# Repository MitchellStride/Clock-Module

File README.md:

# 🐦 Hummingbird RP2040 Clock Module ⏰

The **Hummingbird RP2040 Clock Module** is designed for crafting artisan clocks by pairing it with different clock faces. Its modular design allows this project to be shared across various display technologies.

The test OLED above shows time, my age, and my time to death countdown based on my life expectancy.

---

## 🔧 Features
- Raspberry Pi RP2040 microcontroller with dual-core ARM Cortex-M0+
- Highly compatible with JLCPCB's basic SMT components and 2L stackup for cost
- Powered via USB-C with ESD and reverse polarity protection
- DS1307Z+ RTC with CR2032 coin cell backup
- Single-sided design for a compact, flush mount
- Photocell/LDR support for automatic display dimming
- Additional features: piezoelectric buzzer, RGB LED, power switch, and optional OLED
- FFC expansion for modular clock face integration

---

## 📦 Status
> The PCBA has arrived, and is working, it needed one bodge. FW is done.

---

## 💡 Clock Ideas
Clocks I plan to build using this module:

<details>
<summary>Click to expand</summary>

- **Life Clock:** A countdown to estimated time of death using seven-segment displays
- **Nixie Clock:** A personal take on the classic Nixie tube clock, featuring IN-12 tubes
- **0402 Year Calendar** Inspired by the Yetch THE EVERY DAY GOAL CALENDAR

</details>

---

## 📝 Notes

<details>
<summary>Click to expand</summary>

- I had a few issues with the v1 hardware design since I completed it in roughly two days. Might do a v2.
- From 2024 (schematic design) to 2025 (layout), JLC PCB assembly changed many basic components and increased extended reel fees from $1 → $3, significantly affecting small-run costs.
- The cost per assembled PCB is approximately $8–10 USD, excluding setup fees. A total order of 2 PCBAs + 3 PCBs came to ~$57 + ~$17 shipping. After discounts, the total spent was ~$70 USD, plus $10–20 for extra parts from LCSC or Digikey. The largest expense was reel fees ($30).

See: -> ./images/cost2.png

</details>

---

## 🖼️ Image Appendix

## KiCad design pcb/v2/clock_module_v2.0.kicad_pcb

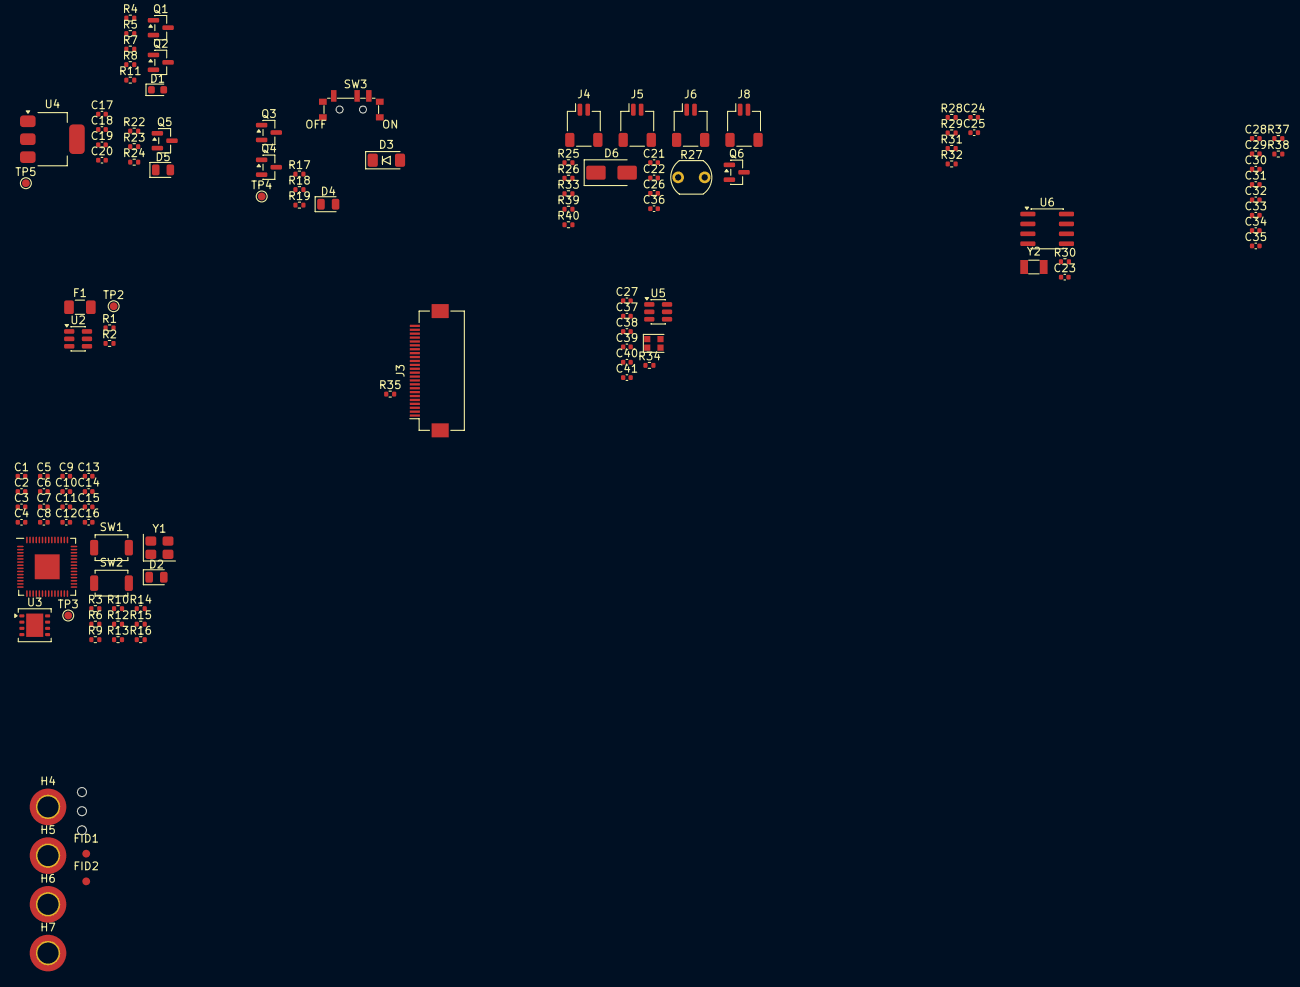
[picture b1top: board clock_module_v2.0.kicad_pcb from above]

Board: 4 copper layers, 121 parts (0 on the bottom side), 65 nets, no tracks yet.

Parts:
C1, C19, C26: 10u; C_0402_1005Metric
C2, C8, C16, C21, C23, C27, C28, C29, C31, C33, C34, C37, C38, C39, C40, C41: 1u; C_0402_1005Metric
C3, C4, C5, C6, C7, C9, C10, C11, C14, C15, C22, C24, C25, C30, C36: 0.1u; C_0402_1005Metric
C12, C13: 10p; C_0402_1005Metric
C17, C18, C20, C35: 4.7u; C_0402_1005Metric
C32: 2.2u; C_0402_1005Metric
D1: Red; LED_0603_1608Metric
D2: YLW; LED_0805_2012Metric
D3: 5.6V; D_MiniMELF
D4, D5: GRN; LED_0805_2012Metric
D6: SS14; D_SMA
D7: WS2812B-2020
F1: 12V 3A; Fuse_1206_3216Metric
FID1, FID2: Fiducial; Fiducial_1mm_Mask2mm
H1, H2, H3: Tooling_Hole_JLC; ToolingHole_1.152mm
H4, H5, H6, H7: Mounting_Hole; MountingHole_2.7mm_M2.5_DIN965_Pad_TopBottom
J3: FFC 24; Hirose_FH12-24S-0.5SH_1x24-1MP_P0.50mm_Horizontal
J4: PWR; JST_SH_SM02B-SRSS-TB_1x02-1MP_P1.00mm_Horizontal
J5: SW; JST_SH_SM02B-SRSS-TB_1x02-1MP_P1.00mm_Horizontal
J6, J8: LDR; JST_SH_SM02B-SRSS-TB_1x02-1MP_P1.00mm_Horizontal
Q1, Q2, Q5, Q6: AO3400A; SOT-23
Q3, Q4: AO3401A; SOT-23
R1, R2: 5.1k; R_0402_1005Metric
R3, R4, R13, R22, R26, R28, R31, R33, R40: 1k; R_0402_1005Metric
R5, R8, R17, R18, R23: 100k; R_0402_1005Metric
R6, R12, R25, R29, R30, R32, R37, R39: 10k; R_0402_1005Metric
R7, R11, R14, R19, R24: 2.2k; R_0402_1005Metric
R9, R10: 22; R_0402_1005Metric
R15, R16: 4.7k; R_0402_1005Metric
R27: GL5516; R_LDR_5.1x4.3mm_P3.4mm_Vertical
R34: 49.9; R_0402_1005Metric
R35: 0; R_0402_1005Metric
R38: 330k; R_0402_1005Metric
SW1, SW2: TS-1187A-B-A-B; SW_SPST_TS-1088-xR020
SW3: SSSS811101
TP2: VBUS; TestPoint_Pad_D1.0mm
TP3: RST; TestPoint_Pad_D1.0mm
TP4: 5V; TestPoint_Pad_D1.0mm
TP5: 3V3; TestPoint_Pad_D1.0mm
U1: RP2040; QFN-56_EP_7x7_Pitch0.4mm
U2: SRV05-4; SOT-23-6
U3: W25Q64JV; WSON-8-1EP_4x4mm_P0.8mm_EP2.2x3mm
U4: AMS1117-3.3; SOT-223-3_TabPin2
U5: SN74LVC1T45DBV; SOT-23-6
U6: DS1307Z+; SOIC-8_3.9x4.9mm_P1.27mm
Y1: XYDBPCNANF-12MHZ; Crystal_SMD_3225-4Pin_3.2x2.5mm
Y2: 32.768kHz; Crystal_SMD_3215-2Pin_3.2x1.5mm

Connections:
+3.3V: C16.1, R12.1, U1.1 (IOVDD), U1.10 (IOVDD), U1.22 (IOVDD), U1.33 (IOVDD), U1.42 (IOVDD), U1.43 (ADC_AVDD), U1.44 (VREG_VIN), U1.48 (USB_VDD), U1.49 (IOVDD), U3.8 (VDD)
+3V3: C1.1, C2.1, C3.1, C4.1, C6.1, C7.1, C9.1, C11.1, C15.1, C19.1, C20.1, C21.1, C28.1, C29.1, C31.1, C38.1, J3.4, R4.1, R6.1, R15.2, R16.2, R22.1, R26.2, R29.1, R30.1, R32.1, R37.1, R40.2, TP5.1, U4.2 (VO), U5.6 (VCCB)
+5V: C17.1, C18.1, C23.1, C26.1, C27.1, C37.1, C39.1, C40.1, C41.1, D6.1 (K), D7.4 (VDD), J3.3, J8.2, Q4.3 (D), R19.2, TP4.1, U4.3 (VI), U5.1 (VCCA), U6.8 (VCC)
/02 RP2040 & USB/D+: R10.2, U1.47 (USB_D+)
/02 RP2040 & USB/D-: R9.2, U1.46 (USB_D-)
/02 RP2040 & USB/GPIO25_LED: R14.2, U1.37 (GPIO25)
/02 RP2040 & USB/QSPI_SCLK: U1.52 (QSPI_SCLK), U3.6 (SCK)
/02 RP2040 & USB/QSPI_SD0: U1.53 (QSPI_SD0), U3.5 (DI/IO0)
/02 RP2040 & USB/QSPI_SD1: U1.55 (QSPI_SD1), U3.2 (DO/IO1)
/02 RP2040 & USB/QSPI_SD2: U1.54 (QSPI_SD2), U3.3 (~WP/IO2)
/02 RP2040 & USB/QSPI_SD3: U1.51 (QSPI_SD3), U3.7 (~HOLD/IO3)
/02 RP2040 & USB/USBBOOT: R13.2, SW2.2
/02 RP2040 & USB/USB_D+: R10.1, U2.3 (IO2)
/02 RP2040 & USB/USB_D-: R9.1, U2.1 (IO1)
/02 RP2040 & USB/~QSPI_CS: R12.2, R13.1, U1.56 (~QSPI_CS), U3.1 (~CS)
/02 RP2040 & USB/~RESET: C5.1, R3.2, R6.2, TP3.1, U1.26 (RUN)
/03 CONNS & PERIPHERALS/BUZZER_LOW: D6.2 (A), J8.1, Q6.3 (D)
/03 CONNS & PERIPHERALS/OLED_RST: C30.1, R37.2
GND: C1.2, C2.2, C3.2, C4.2, C5.2, C6.2, C7.2, C8.2, C9.2, C10.2, C11.2, C12.1, C13.1, C14.2, C15.2, C16.2, C17.2, C18.2, C19.2, C20.2, C21.2, C22.2, C23.2, C24.2, C25.2, C26.2, C27.2, C28.2, C29.2, C30.2, C31.2, C32.1, C35.1, C36.2, C37.2, C38.2, C39.2, C40.2, C41.2, D2.1 (K), D4.1 (K), D7.2 (VSS), J3.2, J3.5, J3.13, J3.18, J3.21, J3.24, J3.MP (MountingPoint), J4.1, J4.MP (Mounting_Point), J5.1, J5.MP (Mounting_Point), J6.MP (Mounting_Point), J8.MP (Mounting_Point), Q1.2 (S), Q2.2 (S), Q5.2 (S), Q6.2 (S), R1.2, R2.2, R5.2, R8.2, R23.2, R25.2, R38.1, R39.2, SW1.2, SW2.1, SW3.1 (A), SW3.2 (B), U1.19 (TESTEN), U1.57 (GND), U2.2 (VN), U3.4 (GND), U3.9 (GND), U4.1 (GND), U5.2 (GND), U5.5 (DIR), U6.4 (GND), Y1.2, Y1.4
GPIO2: J3.8, U1.4 (GPIO2)
GPIO3: J3.9, U1.5 (GPIO3)
GPIO4: J3.10, U1.6 (GPIO4)
GPIO5: J3.11, U1.7 (GPIO5)
GPIO6: J3.12, U1.8 (GPIO6)
GPIO7: J3.14, U1.9 (GPIO7)
GPIO8: J3.15, U1.11 (GPIO8)
GPIO9: J3.16, U1.12 (GPIO9)
GPIO10: J3.17, U1.13 (GPIO10)
GPIO11: R33.2, U1.14 (GPIO11)
GPIO12_PPS: R30.2, U1.15 (GPIO12), U6.7 (SQW/OUT)
GPIO13_WS2812_RGB_LED: U1.16 (GPIO13), U5.4 (B)
GPIO14_BUTTON_0: C24.1, R28.2, R29.2, U1.17 (GPIO14)
GPIO15_BUTTON_1: C25.1, R31.2, R32.2, U1.18 (GPIO15)
GPIO18: J3.19, U1.29 (GPIO18)
GPIO26_ADC0_LDR_EXT: C22.1, J6.1, R25.1, U1.38 (GPIO26)
GPIO27_ADC1_LDR: C36.1, R27.2, R39.1, U1.39 (GPIO27)
GPIO28_ADC2: J3.20, U1.40 (GPIO28)
I2C_SCL: J3.23, R15.1, U1.28 (GPIO17), U6.6 (SCL)
I2C_SDA: J3.22, R16.1, U1.27 (GPIO16), U6.5 (SDA)
unnamed: D1.2 (A), R11.1
unnamed: D1.1 (K), Q2.3 (D)
unnamed: D2.2 (A), R14.1
unnamed: D3.2 (A), Q3.1 (G), Q4.1 (G), R17.1
unnamed: D3.1 (K), Q3.2 (S), Q4.2 (S), R18.1
unnamed: D4.2 (A), R19.1
unnamed: D5.2 (A), R24.1
unnamed: D5.1 (K), Q5.3 (D)
unnamed: D7.3 (DIN), R34.1
unnamed: J3.7, R35.1
unnamed: J6.2, R26.1
unnamed: Q1.3 (D), Q2.1 (G), R7.1, R8.1
unnamed: Q1.1 (G), R4.2, R5.1
unnamed: Q5.1 (G), R22.2, R23.1
unnamed: Q6.1 (G), R33.1
unnamed: R3.1, SW1.1
unnamed: R27.1, R40.1
unnamed: C8.1, C10.1, C14.1, U1.23 (DVDD), U1.45 (VREG_VOUT), U1.50 (DVDD)
unnamed: C12.2, U1.20 (XIN), Y1.3
unnamed: C13.2, U1.21 (XOUT), Y1.1
unnamed: R34.2, U5.3 (A)
unnamed: U6.1 (X1), Y2.2
unnamed: U6.2 (X2), Y2.1
PWR_OFF_SW_N: J5.2, R17.2, R18.2, SW3.3 (C)
UNFUSED_VBUS: F1.2, J4.2
VBUS: F1.1, Q3.3 (D), R7.2, R11.2, R24.2, TP2.1, U2.5 (VP)

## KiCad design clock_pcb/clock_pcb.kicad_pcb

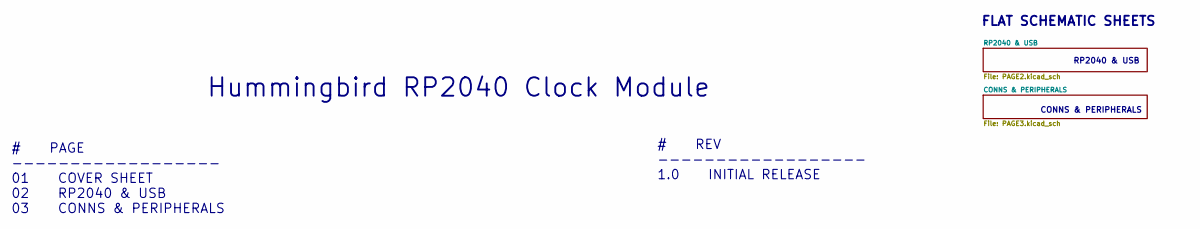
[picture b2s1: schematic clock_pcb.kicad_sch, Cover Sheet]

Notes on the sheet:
RP2040 & USB
CONNS & PERIPHERALS
Hummingbird RP2040 Clock Module
FLAT SCHEMATIC SHEETS
# REV ------------------ 1.0 INITIAL RELEASE
# PAGE ------------------ 01 COVER SHEET 02 RP2040 & USB 03 CONNS & PERIPHERALS

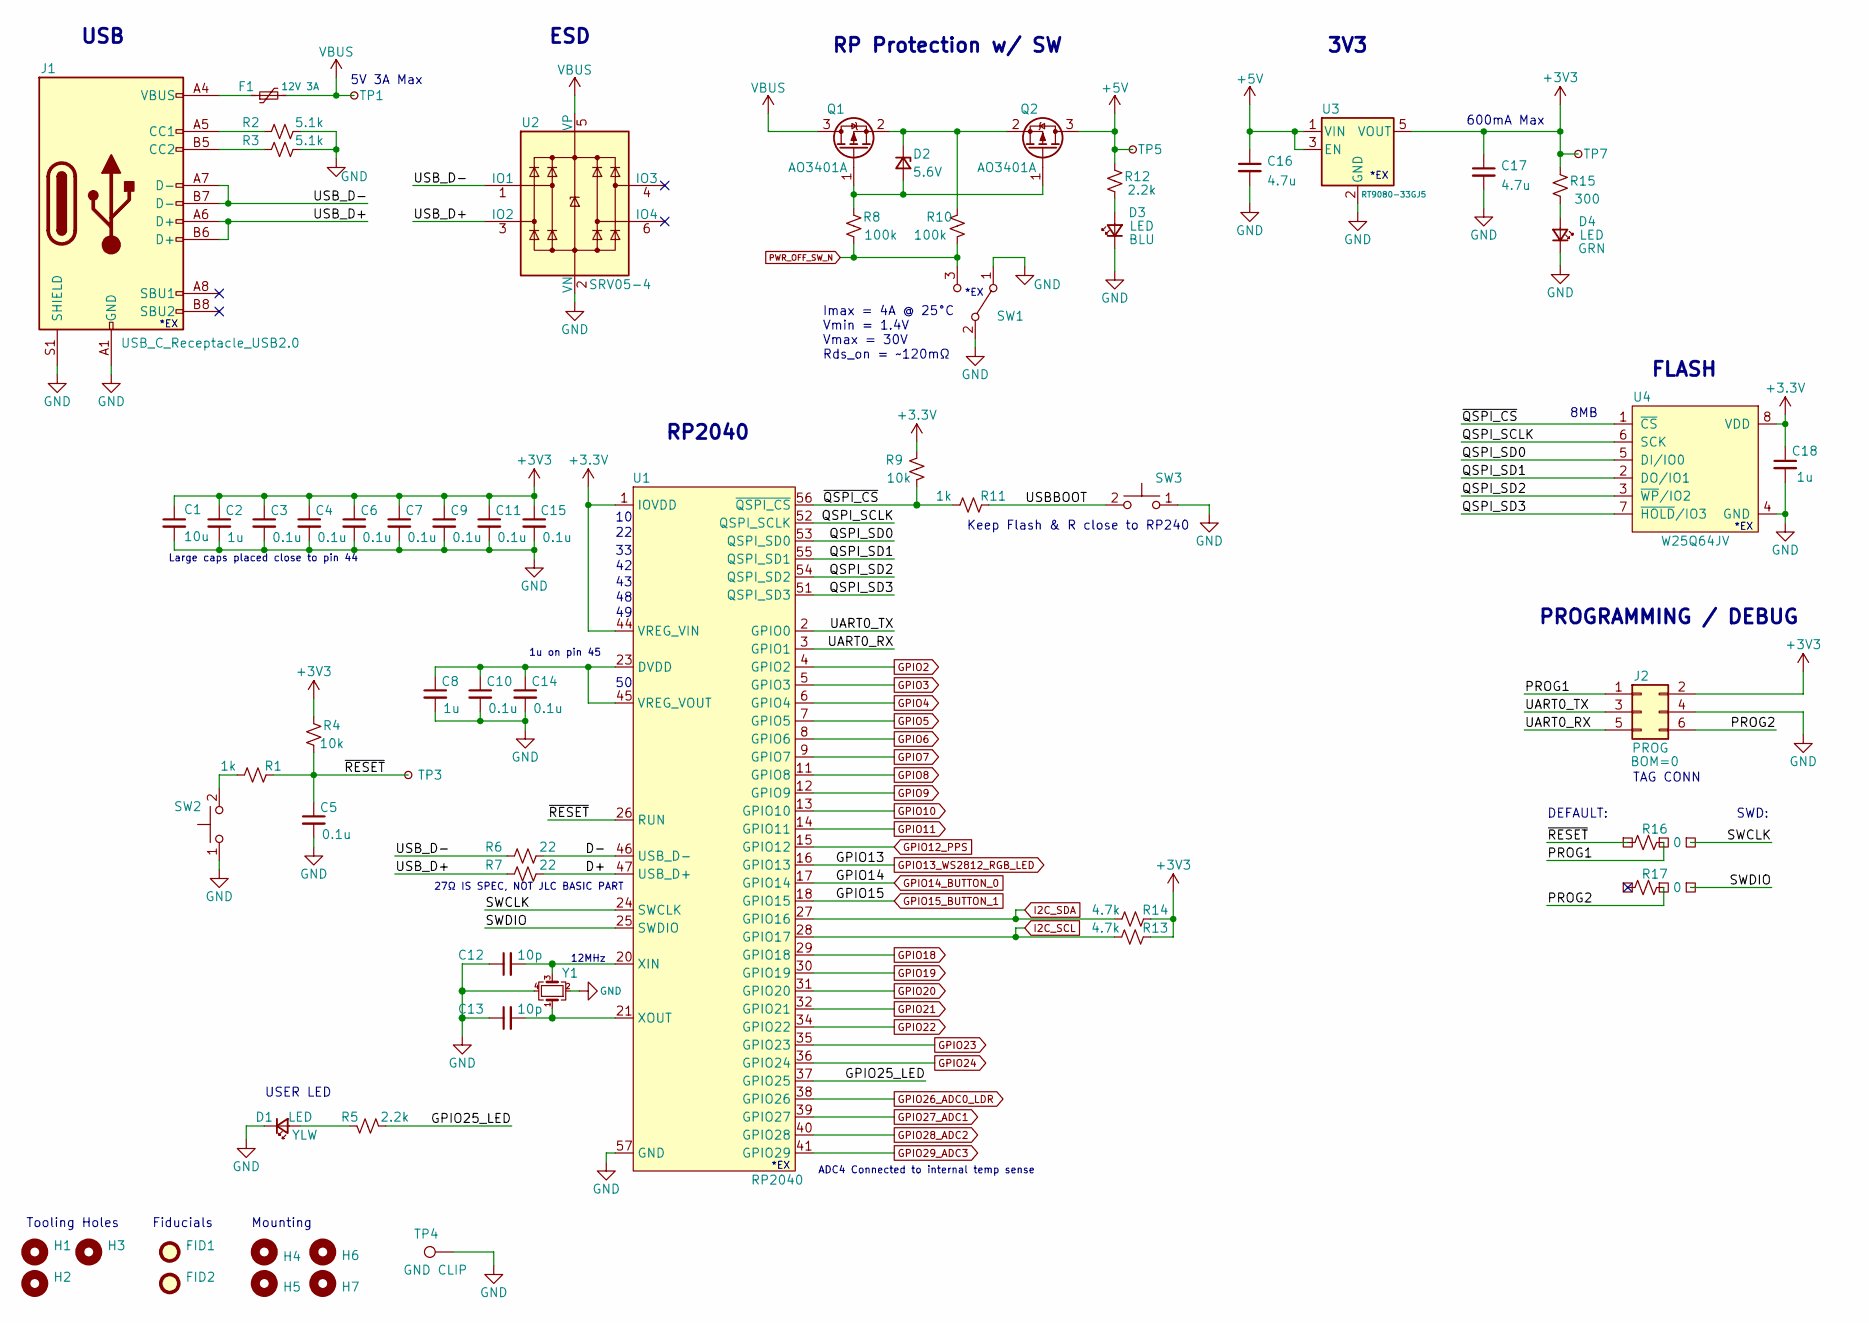
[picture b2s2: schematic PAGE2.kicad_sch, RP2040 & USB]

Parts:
C1: 10u; C_0402_1005Metric; lcsc C15525
C2, C8, C18: 1u; C_0402_1005Metric; lcsc C52923
C3, C4, C5, C6, C7, C9, C10, C11, C14, C15: 0.1u; C_0402_1005Metric; lcsc C1525
C12, C13: 10p; C_0402_1005Metric; lcsc C32949
C16, C17: 4.7u; C_0402_1005Metric; lcsc C23733
D1: LED; LED_0603_1608Metric; lcsc C72038
D2: 5.6V; D_MiniMELF; lcsc C8062
D3: LED; LED_0603_1608Metric; lcsc C72041
D4: LED; LED_0603_1608Metric; lcsc C72043
F1: 12V 3A; Fuse_1206_3216Metric; lcsc C516068
FID1, FID2: Fiducial; Fiducial_1mm_Mask2mm
H1, H2, H3: Tooling_Hole_JLC; JLC_Tooling_Hole
H4, H5, H6, H7: Mounting_Hole; MountingHole_2.7mm_M2.5
J1: USB_C_Receptacle_USB2.0; USB-C-16p_vertical_GT-USB-7051A; lcsc C2843970
J2: PROG; Tag-Connect_TC2030-IDC-NL_2x03_P1.27mm_Vertical
Q1, Q2: AO3401A; SOT-23; lcsc C15127
R1, R11: 1k; R_0402_1005Metric; lcsc C11702
R2, R3: 5.1k; R_0402_1005Metric; lcsc C25744
R4, R9: 10k; R_0402_1005Metric; lcsc C25744
R5, R12: 2.2k; R_0402_1005Metric; lcsc C25879
R6, R7: 22; R_0402_1005Metric; lcsc C25092
R8, R10: 100k; R_0402_1005Metric; lcsc C25741
R13, R14: 4.7k; R_0402_1005Metric; lcsc C25900
R15: 300; R_0402_1005Metric; lcsc C25102
R16, R17: 0; R_0402_1005Metric_3pad; lcsc C17168
SW1: SSSS811101; lcsc C109335
SW2, SW3: TS-1187A-B-A-B; SW_SPST_TL3342_RT; lcsc C318884
TP1: VBUS; TestPoint_Pad_D1.0mm
TP3: RST; TestPoint_Pad_D1.0mm
TP4: GND CLIP; ronghe_RH-5016_C5199799; lcsc C5199799
TP5: 5V; TestPoint_Pad_D1.0mm
TP7: 3V3; TestPoint_Pad_D1.0mm
U1: RP2040; QFN-56_EP_7x7_Pitch0.4mm; lcsc C2040
U2: SRV05-4; SOT-23-6; lcsc C85364
U3: RT9080-33GJ5; SOT-23-5; lcsc C841192
U4: W25Q64JV; WSON-8-1EP_4x4mm_P0.8mm_EP2.2x3mm; lcsc C2940195
Y1: XYDBPCNANF-12MHZ; Crystal_SMD_3225-4Pin_3.2x2.5mm; lcsc C9002

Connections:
+5V: C16.1, Q2.3 (D), R12.2, TP5.1, U3.1 (VIN), U3.3 (EN); also elsewhere on the board
/RP2040 & USB/D+: R7.2, U1.47 (USB_D+)
/RP2040 & USB/D-: R6.2, U1.46 (USB_D-)
/RP2040 & USB/GPIO25_LED: R5.2, U1.37 (GPIO25)
/RP2040 & USB/PROG1: J2.1, R16.2
/RP2040 & USB/PROG2: J2.6, R17.2
/RP2040 & USB/QSPI_SCLK: U1.52 (QSPI_SCLK), U4.6 (SCK)
/RP2040 & USB/QSPI_SD0: U1.53 (QSPI_SD0), U4.5 (DI/IO0)
/RP2040 & USB/QSPI_SD1: U1.55 (QSPI_SD1), U4.2 (DO/IO1)
/RP2040 & USB/QSPI_SD2: U1.54 (QSPI_SD2), U4.3 (~WP/IO2)
/RP2040 & USB/QSPI_SD3: U1.51 (QSPI_SD3), U4.7 (~HOLD/IO3)
/RP2040 & USB/SWCLK: R16.3, U1.24 (SWCLK)
/RP2040 & USB/SWDIO: R17.3, U1.25 (SWDIO)
/RP2040 & USB/UART0_RX: J2.5, U1.3 (GPIO1)
/RP2040 & USB/UART0_TX: J2.3, U1.2 (GPIO0)
/RP2040 & USB/USBBOOT: R11.2, SW3.2
/RP2040 & USB/USB_D+: J1.A6 (D+), J1.B6 (D+), R7.1, U2.3 (IO2)
/RP2040 & USB/USB_D-: J1.A7 (D-), J1.B7 (D-), R6.1, U2.1 (IO1)
/RP2040 & USB/~QSPI_CS: R9.2, R11.1, U1.56 (~QSPI_CS), U4.1 (~CS)
/RP2040 & USB/~RESET: C5.1, R1.2, R4.2, R16.1, TP3.1, U1.26 (RUN)
GND: C1.2, C2.2, C3.2, C4.2, C5.2, C6.2, C7.2, C8.2, C9.2, C10.2, C11.2, C12.1, C13.1, C14.2, C15.2, C16.2, C17.2, C18.2, D1.1 (K), D3.1 (K), D4.1 (K), J1.A1 (GND), J1.A12 (GND), J1.B1 (GND), J1.B12 (GND), J1.S1 (SHIELD), J2.4, R2.2, R3.2, SW1.1 (A), SW1.2 (B), SW2.1, SW3.1, TP4.1, U1.19 (TESTEN), U1.57 (GND), U2.2 (VN), U3.2 (GND), U4.4 (GND), U4.9 (GND), Y1.2, Y1.4; also elsewhere on the board
GPIO2: U1.4 (GPIO2); also elsewhere on the board
GPIO3: U1.5 (GPIO3); also elsewhere on the board
GPIO4: U1.6 (GPIO4); also elsewhere on the board
GPIO5: U1.7 (GPIO5); also elsewhere on the board
GPIO6: U1.8 (GPIO6); also elsewhere on the board
GPIO7: U1.9 (GPIO7); also elsewhere on the board
GPIO8: U1.11 (GPIO8); also elsewhere on the board
GPIO9: U1.12 (GPIO9); also elsewhere on the board
GPIO10: U1.13 (GPIO10); also elsewhere on the board
GPIO11: U1.14 (GPIO11); also elsewhere on the board
GPIO12_PPS: U1.15 (GPIO12)
GPIO13_WS2812_RGB_LED: U1.16 (GPIO13); also elsewhere on the board
GPIO14_BUTTON_0: U1.17 (GPIO14)
GPIO15_BUTTON_1: U1.18 (GPIO15)
GPIO18: U1.29 (GPIO18)
GPIO19: U1.30 (GPIO19)
GPIO20: U1.31 (GPIO20)
GPIO21: U1.32 (GPIO21)
GPIO22: U1.34 (GPIO22)
GPIO23: U1.35 (GPIO23)
GPIO24: U1.36 (GPIO24)
GPIO26_ADC0_LDR: U1.38 (GPIO26); also elsewhere on the board
GPIO27_ADC1: U1.39 (GPIO27); also elsewhere on the board
GPIO28_ADC2: U1.40 (GPIO28); also elsewhere on the board
GPIO29_ADC3: U1.41 (GPIO29)
I2C_SCL: R13.1, U1.28 (GPIO17); also elsewhere on the board
I2C_SDA: R14.1, U1.27 (GPIO16); also elsewhere on the board
unnamed: D1.2 (A), R5.1
unnamed: D2.2 (A), Q1.1 (G), Q2.1 (G), R8.1
unnamed: D2.1 (K), Q1.2 (S), Q2.2 (S), R10.1
unnamed: D3.2 (A), R12.1
unnamed: D4.2 (A), R15.1
unnamed: F1.1, J1.A4 (VBUS), J1.A9 (VBUS), J1.B4 (VBUS), J1.B9 (VBUS)
unnamed: J1.A5 (CC1), R2.1
unnamed: J1.B5 (CC2), R3.1
unnamed: R1.1, SW2.2
unnamed: C8.1, C10.1, C14.1, U1.23 (DVDD), U1.45 (VREG_VOUT), U1.50 (DVDD)
unnamed: C12.2, U1.20 (XIN), Y1.3
unnamed: C13.2, U1.21 (XOUT), Y1.1
PWR_OFF_SW_N: R8.2, R10.2, SW1.3 (C); also elsewhere on the board
VBUS: F1.2, Q1.3 (D), TP1.1, U2.5 (VP); also elsewhere on the board

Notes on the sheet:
12MHz
5V 3A Max
3V3
8MB
*EX
Imax = 4A @ 25°C Vmin = 1.4V Vmax = 30V Rds_on = ~120mΩ
RP Protection w/ SW
27Ω IS SPEC, NOT JLC BASIC PART
Tooling Holes
ADC4 Connected to internal temp sense
ESD
Keep Flash & R close to RP240
USB
TAG CONN
Mounting
Large caps placed close to pin 44
FLASH
DEFAULT:
1u on pin 45
RP2040
600mA Max
USER LED
Fiducials
PROGRAMMING / DEBUG
SWD:

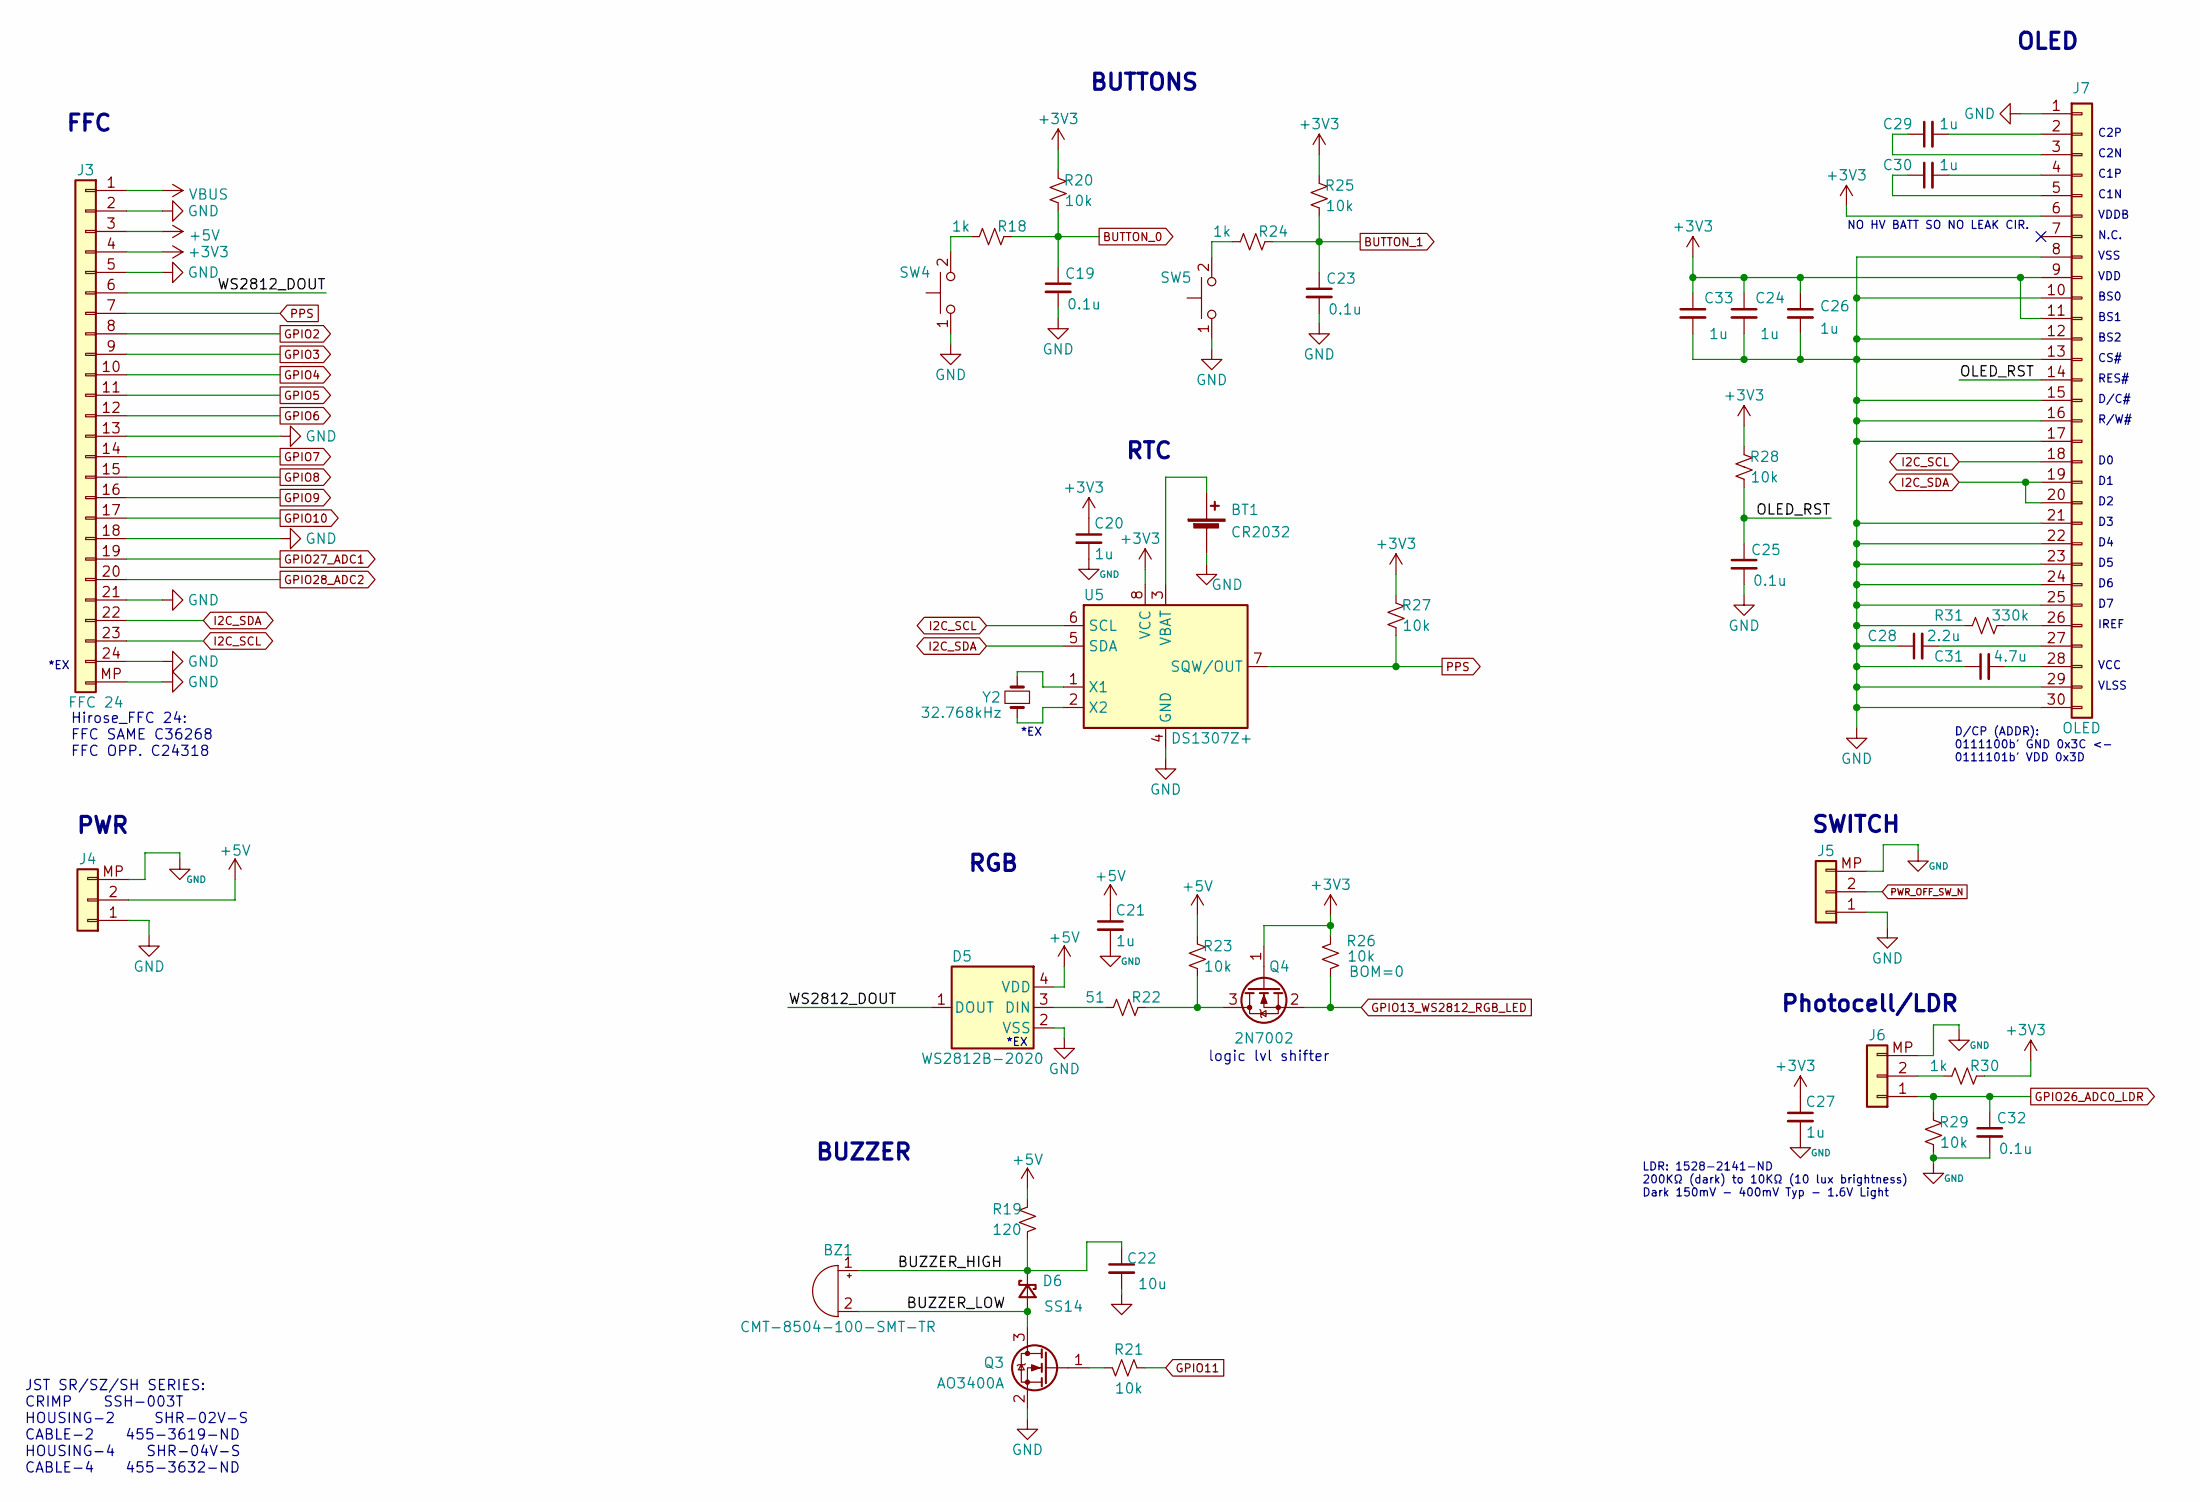
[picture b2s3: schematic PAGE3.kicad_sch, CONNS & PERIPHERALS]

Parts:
BT1: CR2032; Q&J_CR2032-BS-6-1; lcsc C70377
BZ1: CMT-8504-100-SMT-TR; MagneticBuzzer_CUI_CMT-8504-100-SMT; digi 102-CMT-8504-100-SMT-CT-ND
C19, C23, C25, C32: 0.1u; C_0402_1005Metric; lcsc C1525
C20, C21, C24, C26, C27, C29, C30, C33: 1u; C_0402_1005Metric; lcsc C52923
C22: 10u; C_0402_1005Metric; lcsc C15525
C28: 2.2u; C_0402_1005Metric; lcsc C12530
C31: 4.7u; C_0402_1005Metric; lcsc C23733
D5: WS2812B-2020; lcsc C965555
D6: SS14; D_SMA; lcsc C2480
J3: FFC 24; Hirose_FH12-24S-0.5SH_1x24-1MP_P0.50mm_Horizontal; lcsc C202112
J4, J5, J6: 5V; JST_SH_SM02B-SRSS-TB_1x02-1MP_P1.00mm_Horizontal; lcsc C160402
J7: OLED; OLED-128O064D_edit_reverse_v2; lcsc C2890596
Q3: AO3400A; SOT-23; lcsc C20917
Q4: 2N7002; SOT-23; lcsc C8545
R18, R24, R30: 1k; R_0402_1005Metric; lcsc C11702
R19: 120; R_0402_1005Metric; lcsc C25079
R20, R21, R23, R25, R26, R27, R28, R29: 10k; R_0402_1005Metric; lcsc C25744
R22: 51; R_0402_1005Metric; lcsc C25125
R31: 330k; R_0402_1005Metric; lcsc C25778
SW4, SW5: TS-1187A-B-A-B; SW_SPST_TL3342_RT; lcsc C318884
U5: DS1307Z+; SOIC-8_3.9x4.9mm_P1.27mm; lcsc C8959
Y2: 32.768kHz; Crystal_SMD_3215-2Pin_3.2x1.5mm; lcsc C95361

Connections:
+5V: C21.1, D5.4 (VDD), J3.3, J4.2, R19.1, R23.1; also elsewhere on the board
/CONNS & PERIPHERALS/BUZZER_HIGH: BZ1.1 (-), C22.1, D6.1 (K), R19.2
/CONNS & PERIPHERALS/BUZZER_LOW: BZ1.2 (+), BZ1.3 (DUMMY1), BZ1.4 (DUMMY2), D6.2 (A), Q3.3 (D)
/CONNS & PERIPHERALS/OLED_RST: C25.1, J7.14, R28.2
/CONNS & PERIPHERALS/WS2812_DOUT: D5.1 (DOUT), J3.6
BUTTON_0: C19.1, R18.2, R20.2
BUTTON_1: C23.1, R24.2, R25.2
GND: BT1.2 (-), C19.2, C20.2, C21.2, C22.2, C23.2, C24.2, C25.2, C26.2, C27.2, C28.1, C31.1, C32.2, C33.2, D5.2 (VSS), J3.2, J3.5, J3.13, J3.18, J3.21, J3.24, J3.MP (MountingPoint), J4.1, J4.MP (Mounting_Point), J5.1, J5.MP (Mounting_Point), J6.MP (Mounting_Point), J7.1, J7.8, J7.10, J7.12, J7.13, J7.15, J7.16, J7.17, J7.21, J7.22, J7.23, J7.24, J7.25, J7.29, J7.30, Q3.2 (S), R29.2, R31.1, SW4.1, SW5.1, U5.4 (GND); also elsewhere on the board
GPIO2: J3.8; also elsewhere on the board
GPIO3: J3.9; also elsewhere on the board
GPIO4: J3.10; also elsewhere on the board
GPIO5: J3.11; also elsewhere on the board
GPIO6: J3.12; also elsewhere on the board
GPIO7: J3.14; also elsewhere on the board
GPIO8: J3.15; also elsewhere on the board
GPIO9: J3.16; also elsewhere on the board
GPIO10: J3.17; also elsewhere on the board
GPIO11: R21.1; also elsewhere on the board
GPIO13_WS2812_RGB_LED: Q4.2 (S), R26.2; also elsewhere on the board
GPIO26_ADC0_LDR: C32.1, J6.1, R29.1; also elsewhere on the board
GPIO27_ADC1: J3.19; also elsewhere on the board
GPIO28_ADC2: J3.20; also elsewhere on the board
I2C_SCL: J3.23, J7.18, U5.6 (SCL); also elsewhere on the board
I2C_SDA: J3.22, J7.19, J7.20, U5.5 (SDA); also elsewhere on the board
unnamed: BT1.1 (+), U5.3 (VBAT)
unnamed: D5.3 (DIN), R22.1
unnamed: J6.2, R30.1
unnamed: C29.2, J7.2
unnamed: C29.1, J7.3
unnamed: C30.2, J7.4
unnamed: C30.1, J7.5
unnamed: J7.26, R31.2
unnamed: C28.2, J7.27
unnamed: C31.2, J7.28
unnamed: Q3.1 (G), R21.2
unnamed: Q4.3 (D), R22.2, R23.2
unnamed: R18.1, SW4.2
unnamed: R24.1, SW5.2
unnamed: U5.1 (X1), Y2.2
unnamed: U5.2 (X2), Y2.1
PPS: J3.7, R27.2, U5.7 (SQW/OUT)
PWR_OFF_SW_N: J5.2; also elsewhere on the board
VBUS: J3.1; also elsewhere on the board

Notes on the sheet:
VCC
BS2
PWR
OLED
*EX
SWITCH
BUZZER
RES#
R/W#
C1N
CS#
Photocell/LDR
NO HV BATT SO NO LEAK CIR.
logic lvl shifter
BS1
FFC
IREF
D/CP (ADDR): 0111100b' GND 0x3C <- 0111101b' VDD 0x3D
D/C#
VDDB
BS0
C2N
RTC
C1P
BUTTONS
LDR: 1528-2141-ND 200KΩ (dark) to 10KΩ (10 lux brightness) Dark 150mV - 400mV Typ - 1.6V Light
Hirose_FFC 24: FFC SAME C36268 FFC OPP. C24318
VLSS
VSS
C2P
JST SR/SZ/SH SERIES: CRIMP SSH-003T HOUSING-2 SHR-02V-S CABLE-2 455-3619-ND HOUSING-4 SHR-04V-S CABLE-4 455-3632-ND
N.C.
RGB
VDD

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
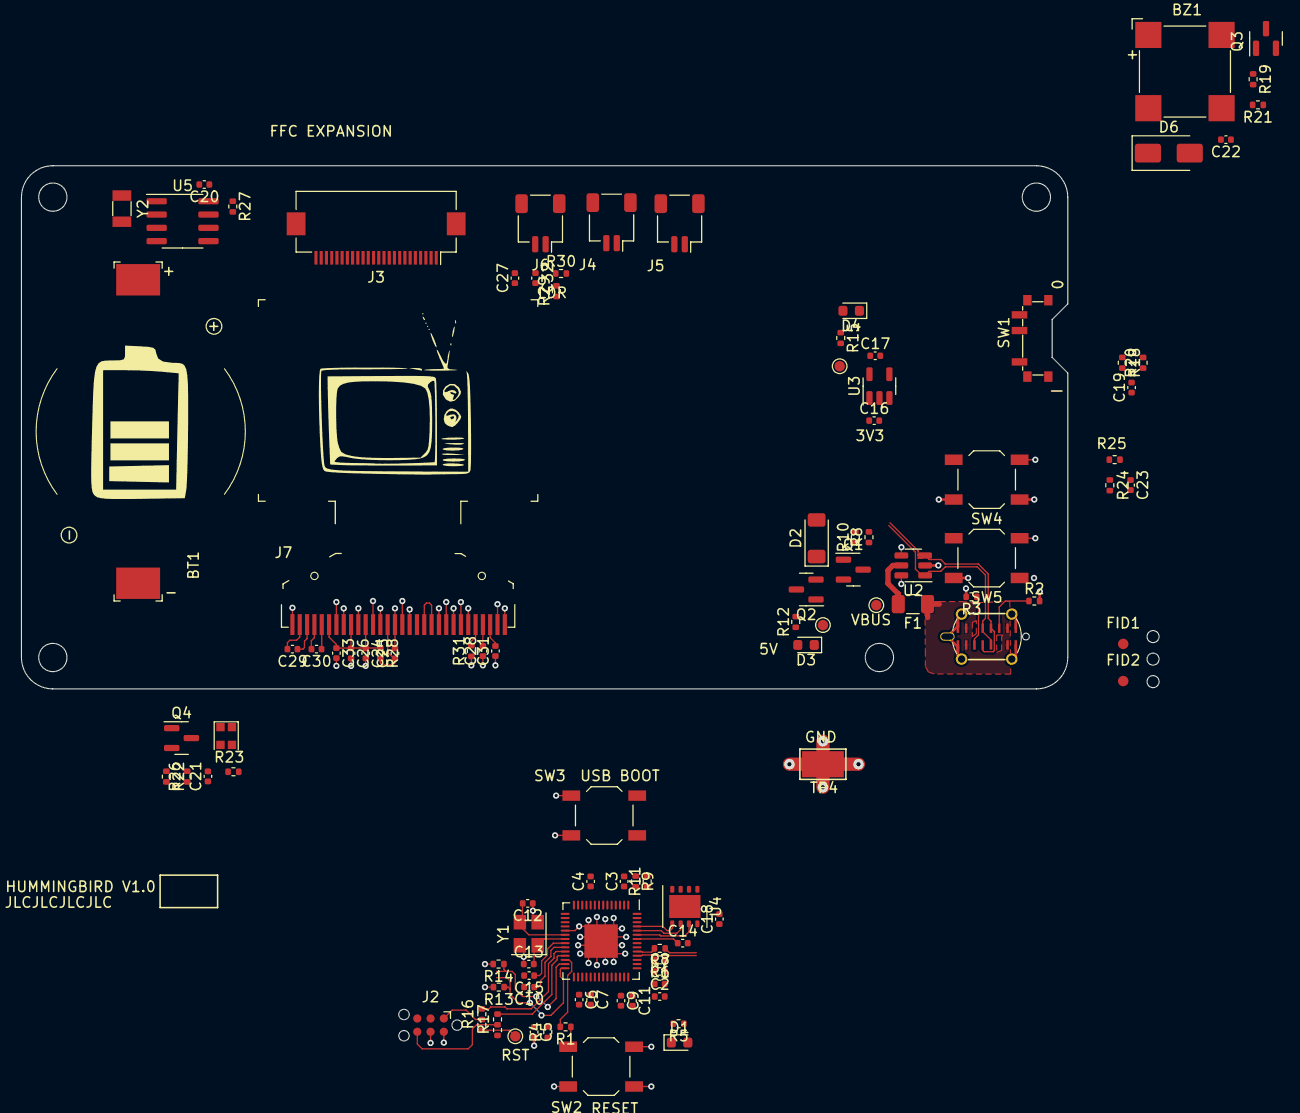
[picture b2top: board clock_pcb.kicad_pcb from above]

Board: 2 copper layers, 100.0 x 50.0 mm, 110 parts (0 on the bottom side), 75 nets.

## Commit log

2023-04-19 split from other deathclock repo
2023-06-19 finished schematic parts, layout outline
2023-06-19 image cleanup
2023-06-21 changed all to single sided
2023-06-22 layout work
2023-06-28 fusion360 assm is not nice
2025-05-10 Routed, no gerbers
2025-05-12 Ordered pcba
2025-05-12 fix readme img link
2025-05-13 Updating todo
2025-05-28 PCBA arrived, blinking
2025-12-09 firmware dev and hw fixes
2025-12-12 completion
2025-12-12 readme fix img
2025-12-12 img adjustment and readme fix2
2025-12-12 adjust readme badges
2025-12-22 v2 org
2025-12-22 started v2
2025-12-23 schematic pick

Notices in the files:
README.md:
License: CC BY-NC-SA
